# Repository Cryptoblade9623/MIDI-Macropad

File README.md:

# MIDI-Macropad
A MIDI macropad with 6 mechanical switches, per-key RGB, a rotary encoder and 7 capacitive touch keys. 
It is powered using a 2000mah battery and a TP4056 module. It is controlled by a Waveshare ESP32-S3-Zero. It can turn on and off using a rocker switch. 
This is a project for Half-Life at Hack club. This project's guide was made by [Kai Pereira](https://github.com/KaiPereira).
I have made my adjustments from the original project like adding more switches, more LEDs, making a themed case and making it battery powered. 
As I already have the keycaps and rocker switches and I will buy the lights and case myself, I will not include them in the Half-Life BOM, but they will be located in the readme for anyone who wants to make it from scratch. 
The files will include all 3D models used ( 3D printed parts and separate models online that i used for designing ), KiCad files and firmware. 
I tried to make as much as I could with the use of LLMs and I almost finished but I had to use AI to code the capacitive touch keys because I couldn't find documentation for that anywhere.
Everything but the capacitive touch keys section is code written/typed by hand.
The images below are screenshots of: what the project should look like after finished, PCB 3D models, offboard wired components, KiCad PCB and KiCad schematics in that order.

| Item                       | Qty | Supplier                   | Cost/item | Total Cost | link                                                                                                                                                                                                                                                                                                                                                                                                                                                                                                                                                                                                                                                                                                                                                                                                                                                                                                                                                                                                                 |
|----------------------------|-----|----------------------------|-----------|------------|----------------------------------------------------------------------------------------------------------------------------------------------------------------------------------------------------------------------------------------------------------------------------------------------------------------------------------------------------------------------------------------------------------------------------------------------------------------------------------------------------------------------------------------------------------------------------------------------------------------------------------------------------------------------------------------------------------------------------------------------------------------------------------------------------------------------------------------------------------------------------------------------------------------------------------------------------------------------------------------------------------------------|
| EC11 Rotary Encoder        | 1   | AliExpress                 | $2.04     | $2.04      | https://www.aliexpress.com/item/1005008973821901.html?spm=a2g0o.productlist.main.61.5bdd101emPDBlZ&algo_pvid=73940321-b95f-4575-a293-c059ac68aa32&algo_exp_id=73940321-b95f-4575-a293-c059ac68aa32-58&pdp_ext_f=%7B%22order%22%3A%2242%22%2C%22eval%22%3A%221%22%2C%22fromPage%22%3A%22search%22%7D&pdp_npi=6%40dis%21USD%212.04%212.03%21%21%2113.57%2113.50%21%4021038a9c17927755863875781e0e0a%2112000047424950599%21sea%21GB%210%21ABX%211%210%21n_tag%3A-29910%3Bd%3Ad6cd2d24%3Bm03_new_user%3A-29895%3BpisId%3A5000000218644952&curPageLogUid=blD9KSLR4E14&utparam-url=scene%3Asearch%7Cquery_from%3A%7Cx_object_id%3A1005008973821901%7C_p_origin_prod%3A                                                                                                                                                                                                                                                                                                                  |
| ESP32-S3-Zero              | 1   | AliExpress                 | $4.76     | $4.76      | https://www.aliexpress.com/item/1005007948911104.html?spm=a2g0o.productlist.main.29.238369f4yT16e8&algo_pvid=caeeea92-3d00-4a40-bc0e-dfc0eba1c6cb&algo_exp_id=caeeea92-3d00-4a40-bc0e-dfc0eba1c6cb-28&pdp_ext_f=%7B%22order%22%3A%221234%22%2C%22spu_best_type%22%3A%22price%22%2C%22eval%22%3A%221%22%2C%22fromPage%22%3A%22search%22%7D&pdp_npi=6%40dis%21USD%213.62%213.61%21%21%2124.06%2123.99%21%402103849717926670627467357e0dee%2112000051591697058%21sea%21GB%210%21ABX%211%210%21n_tag%3A-29910%3Bd%3Ad6cd2d24%3Bm03_new_user%3A-29895%3BpisId%3A5000000218644952&curPageLogUid=fZAsHxCwW0Vm&utparam-url=scene%3Asearch%7Cquery_from%3A%7Cx_object_id%3A1005007948911104%7C_p_origin_prod%3A                                                                                                                                                                                                                                                                                                               |
| OUTEMU Mechanical Switches | 1   | AliExpress                 | $3.48     | $3.48      | https://www.aliexpress.com/item/1005008210158349.html?spm=a2g0o.productlist.main.1.431a286fu5XIFE&algo_pvid=c54de943-8488-4a99-b3c9-1087a205fbdd&algo_exp_id=c54de943-8488-4a99-b3c9-1087a205fbdd-0&pdp_ext_f=%7B%22order%22%3A%22342%22%2C%22eval%22%3A%221%22%2C%22fromPage%22%3A%22search%22%7D&pdp_npi=6%40dis%21USD%213.48%211.35%21%21%213.48%211.35%21%402103828617924316227855893e10b3%2112000044245885241%21sea%21GB%210%21ABX%211%210%21n_tag%3A-29910%3Bd%3Ad6cd2d24%3Bm03_new_user%3A-29895%3BpisId%3A5000000218643717&curPageLogUid=KWfBJ2vS2QvT&utparam-url=scene%3Asearch%7Cquery_from%3A%7Cx_object_id%3A1005008210158349%7C_p_origin_prod%3A                                                                                                                                                                                                                                                                                                                                                        |
| PCB                        | 1   | JLCPCB                     | $9.10     | $9.10      | https://cart.jlcpcb.com/shopcart/cartEdit/?id=0b54ba9c2a9749e79611989d17219a13&type=1&changeType=1&achieveDate=72                                                                                                                                                                                                                                                                                                                                                                                                                                                                                                                                                                                                                                                                                                                                                                                                                                                                                                    |
| TP4056 Module              | 1   | AliExpress                 | $1.11     | $1.11      | https://www.aliexpress.com/item/1005012010859998.html?spm=a2g0o.detail.pcDetailTopMoreOtherSeller.7.8b4fs1gQs1gQMz&gps-id=pcDetailTopMoreOtherSeller&scm=1007.40050.354490.0&scm_id=1007.40050.354490.0&scm-url=1007.40050.354490.0&pvid=6702e870-a7da-431f-965d-711fee851179&_t=gps-id%3ApcDetailTopMoreOtherSeller%2Cscm-url%3A1007.40050.354490.0%2Cpvid%3A6702e870-a7da-431f-965d-711fee851179%2Ctpp_buckets%3A668%232846%238115%232000&pdp_ext_f=%7B%22order%22%3A%224080%22%2C%22eval%22%3A%221%22%2C%22orig_sl_item_id%22%3A%221005012010859998%22%2C%22orig_item_id%22%3A%221005012545578213%22%2C%22sceneId%22%3A%2230050%22%2C%22fromPage%22%3A%22recommend%22%7D&pdp_npi=6%40dis%21USD%212.23%211.11%21%21%2114.83%217.42%21%4021038db317926605102783847e0f16%2112000059351234419%21rec%21GB%21%21ABX%211%210%21n_tag%3A-29910%3Bd%3Ad6cd2d24%3Bm03_new_user%3A-29895&utparam-url=scene%3ApcDetailTopMoreOtherSeller%7Cquery_from%3A%7Cx_object_id%3A1005012010859998%7C_p_origin_prod%3A1005012545578213 |
| Battery                    | 1   | AliExpress                 | $5.99     | $5.99      | https://www.aliexpress.com/item/1005005614561610.html?spm=a2g0o.detail.pcDetailTopMoreOtherSeller.10.47f71UA91UA9tm&gps-id=pcDetailTopMoreOtherSeller&scm=1007.40050.354490.0&scm_id=1007.40050.354490.0&scm-url=1007.40050.354490.0&pvid=a5e69e93-03ff-41cb-8222-ed78d5e98786&_t=gps-id%3ApcDetailTopMoreOtherSeller%2Cscm-url%3A1007.40050.354490.0%2Cpvid%3Aa5e69e93-03ff-41cb-8222-ed78d5e98786%2Ctpp_buckets%3A668%232846%238111%231996&pdp_ext_f=%7B%22order%22%3A%22664%22%2C%22eval%22%3A%221%22%2C%22sceneId%22%3A%2230050%22%2C%22fromPage%22%3A%22recommend%22%7D&pdp_npi=6%40dis%21USD%215.99%211.35%21%21%215.99%211.35%21%40210381f017926611875426069e0e8c%2112000040028049695%21rec%21GB%21%21ABXZ%211%210%21n_tag%3A-29910%3Bd%3Ad6cd2d24%3Bm03_new_user%3A-29895%3BpisId%3A5000000218642852&utparam-url=scene%3ApcDetailTopMoreOtherSeller%7Cquery_from%3A%7Cx_object_id%3A1005005614561610%7C_p_origin_prod%3A                                                                                     |
| SK6812MINI-E RGB Lights    | 10  | Alibaba                    | $0.16     | $1.60      | https://www.alibaba.com/product-detail/Good-Quality-RGB-LED-SK6812MINI-E_1601785986306.html?spm=a2756.trade-carp.valid-supplier.2.21183192jbIMls                                                                                                                                                                                                                                                                                                                                                                                                                                                                                                                                                                                                                                                                                                                                                                                                                                                                     |
| 3D Printed Case            | 1   | Printer on Printing Legion | $2.67     | $2.67      | https://app.slack.com/client/E09V59WQY1E/C083P4FJM46                                                                                                                                                                                                                                                                                                                                                                                                                                                                                                                                                                                                                                                                                                                                                                                                                                                                                                                                                                 |
| Estimated total shipping   | 1   |                            |           | $6.06      |                                                                                                                                                                                                                                                                                                                                                                                                                                                                                                                                                                                                                                                                                                                                                                                                                                                                                                                                                                                                                      |
| Grand Total                |     |                            |           | $36.04     |                                                                                                                                                                                                                                                                                                                                                                                                                                                                                                                                                                                                                                                                                                                                                                                                                                                                                                                                                                                                                      |

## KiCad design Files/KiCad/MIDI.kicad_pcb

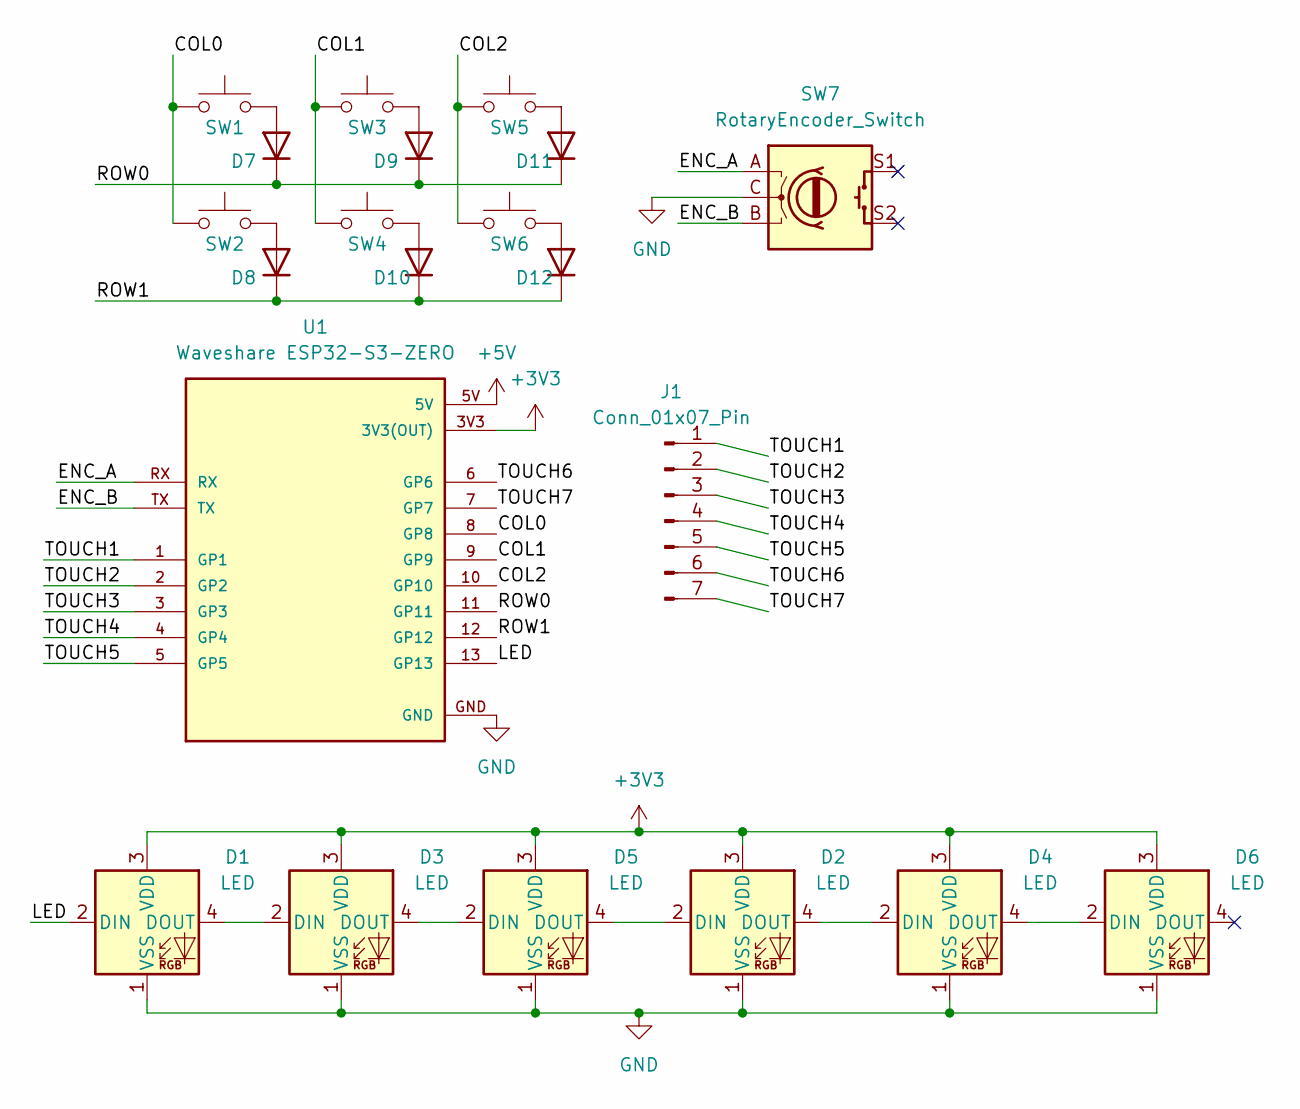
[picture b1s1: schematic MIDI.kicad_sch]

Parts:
D1, D2, D3, D4, D5, D6: LED; LED_MX_6028R
D7, D8, D9, D10, D11, D12: D; D_SOD-123
J1: Conn_01x07_Pin; Capacitive_PADS_7_25mm
SW1, SW2, SW3, SW4, SW5, SW6: SW_Push; SW_MX_HS_CPG151101S11_1u
SW7: RotaryEncoder_Switch; RotaryEncoder_Alps_EC11E-Switch_Vertical_H20mm
U1: Waveshare ESP32-S3-ZERO; Waveshare ESP32-S3-Zero; PARTREV NA

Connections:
+3V3: D1.3 (VDD), D2.3 (VDD), D3.3 (VDD), D4.3 (VDD), D5.3 (VDD), D6.3 (VDD), U1.3V3 (3V3(OUT))
+5V: U1.5V
/COL0: SW1.1, SW2.1, U1.8 (GP8)
/COL1: SW3.1, SW4.1, U1.9 (GP9)
/COL2: SW5.1, SW6.1, U1.10 (GP10)
/ENC_A: SW7.A, U1.RX
/ENC_B: SW7.B, U1.TX
/LED: D1.2 (DIN), U1.13 (GP13)
/ROW0: D7.1 (K), D9.1 (K), D11.1 (K), U1.11 (GP11)
/ROW1: D8.1 (K), D10.1 (K), D12.1 (K), U1.12 (GP12)
/TOUCH1: J1.1, U1.1 (GP1)
/TOUCH2: J1.2, U1.2 (GP2)
/TOUCH3: J1.3, U1.3 (GP3)
/TOUCH4: J1.4, U1.4 (GP4)
/TOUCH5: J1.5, U1.5 (GP5)
/TOUCH6: J1.6, U1.6 (GP6)
/TOUCH7: J1.7, U1.7 (GP7)
GND: D1.1 (VSS), D2.1 (VSS), D3.1 (VSS), D4.1 (VSS), D5.1 (VSS), D6.1 (VSS), SW7.C, U1.GND
unnamed: D1.4 (DOUT), D3.2 (DIN)
unnamed: D2.2 (DIN), D5.4 (DOUT)
unnamed: D2.4 (DOUT), D4.2 (DIN)
unnamed: D3.4 (DOUT), D5.2 (DIN)
unnamed: D4.4 (DOUT), D6.2 (DIN)
unnamed: D7.2 (A), SW1.2
unnamed: D8.2 (A), SW2.2
unnamed: D9.2 (A), SW3.2
unnamed: D10.2 (A), SW4.2
unnamed: D11.2 (A), SW5.2
unnamed: D12.2 (A), SW6.2

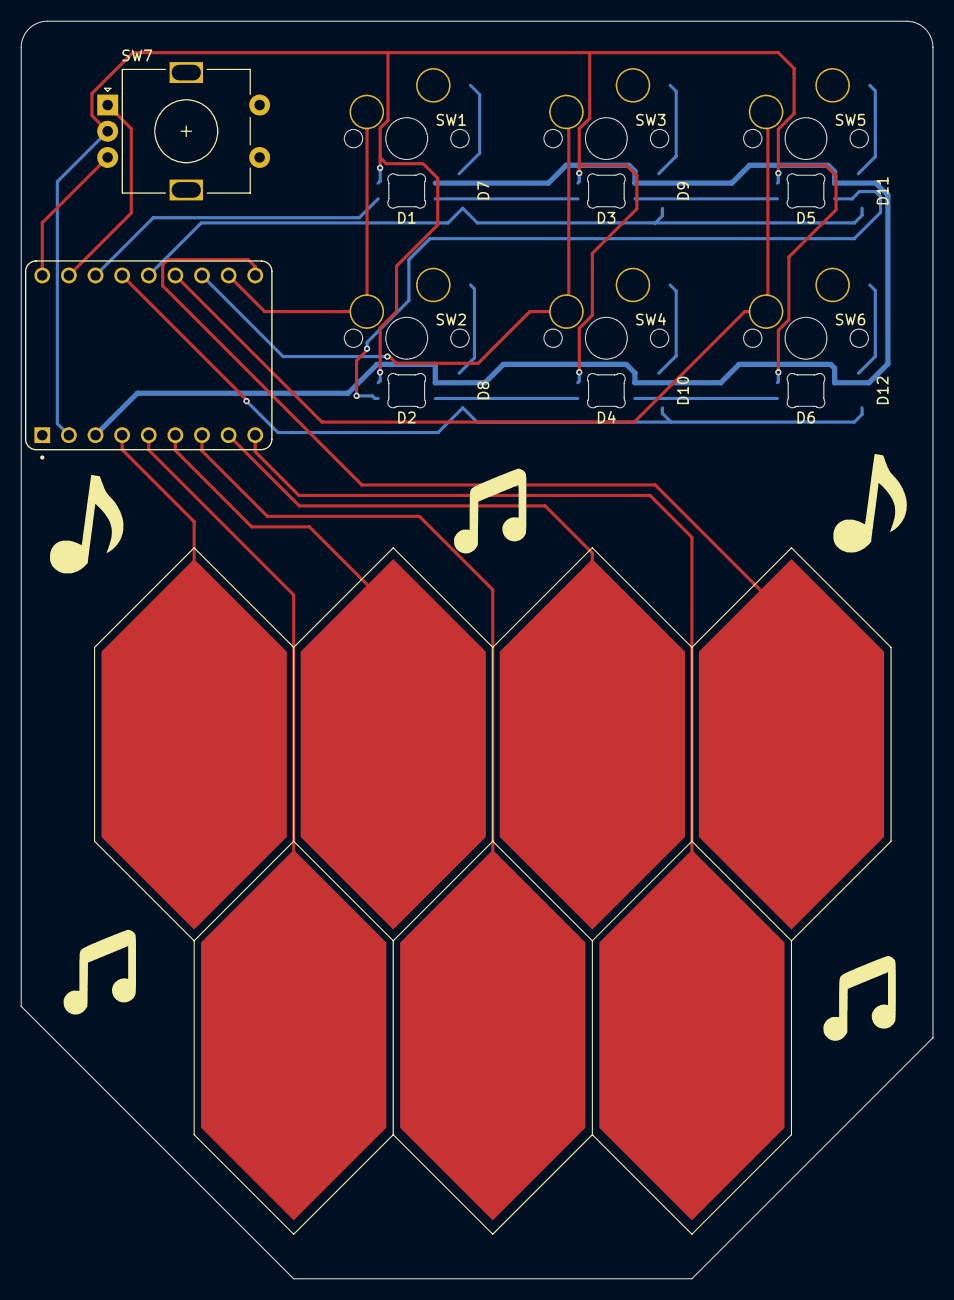
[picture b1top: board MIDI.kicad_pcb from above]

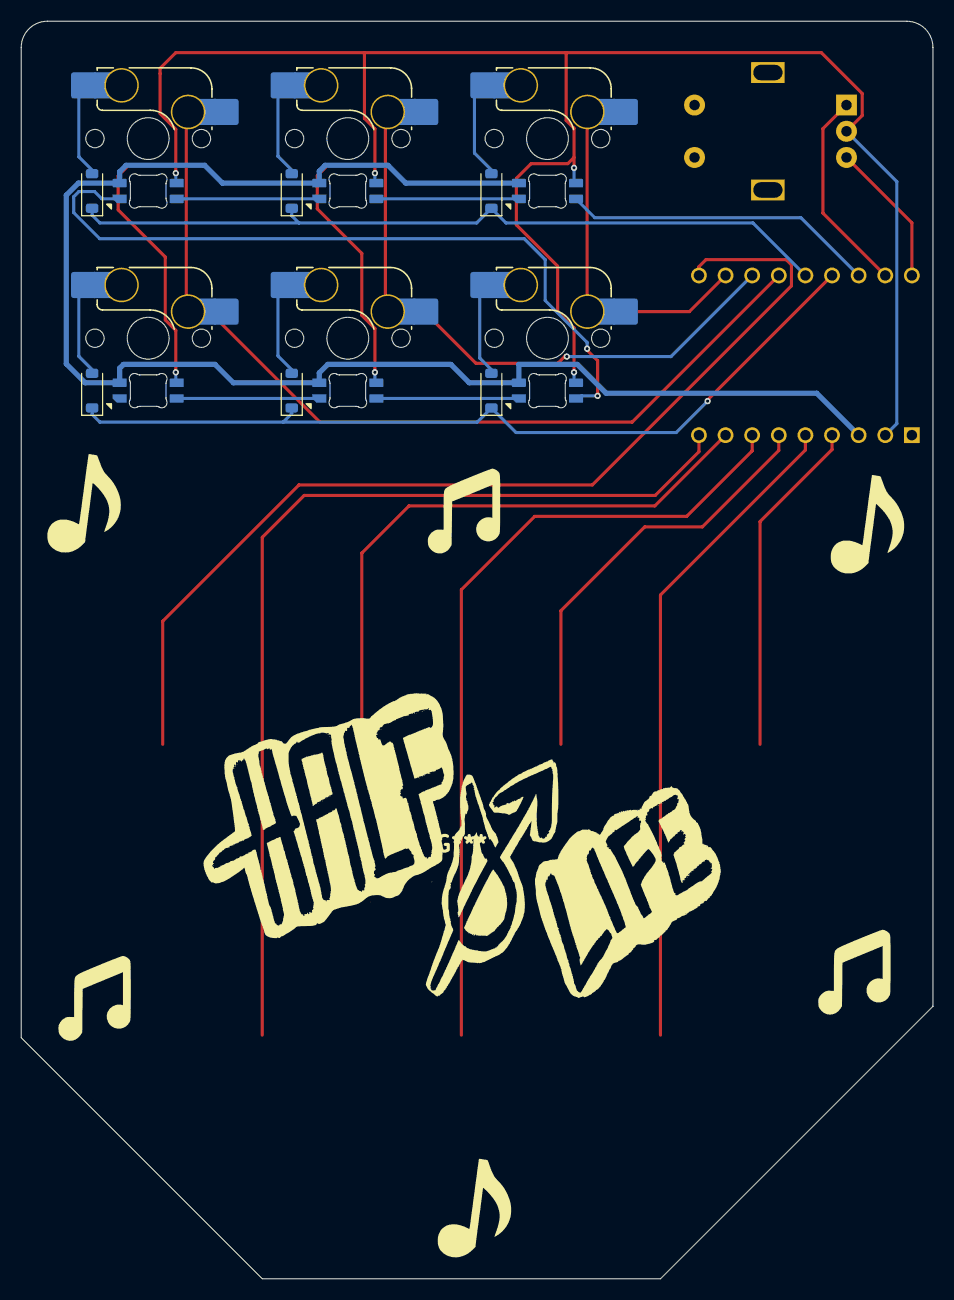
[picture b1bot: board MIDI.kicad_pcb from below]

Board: 2 copper layers, 87.0 x 120.0 mm, 21 parts (18 on the bottom side), 28 nets.

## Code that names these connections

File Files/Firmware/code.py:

print("Starting")

import board
import touchio

from kmk.kmk_keyboard import KMKKeyboard
from kmk.keys import KC
from kmk.scanners import DiodeOrientation
from kmk.modules.encoder import EncoderHandler
from kmk.extensions.rgb import RGB
from kmk.extensions.rgb import AnimationModes
from kmk.extensions.media_keys import MIDI
from kmk.extensions import Extension

keyboard = KMKKeyboard()

COL1 = board.IO8
COL2 = board.IO9
COL3 = board.IO10
ROW1 = board.IO11
ROW2 = board.IO12
ENC_A = board.RX
ENC_B = board.TX
LED = board.IO13

TOUCH_PINS = [
    board.IO1, 
    board.IO2, 
    board.IO3, 
    board.IO4, 
    board.IO5, 
    board.IO6, 
    board.IO7, 
]

TOUCH_NOTES = [60, 62, 64, 65, 67, 69, 71]

class CapacitiveTouchMidi(Extension):
    def __init__(self, pins, notes):
        self.touch_pads = [touchio.TouchIn(pin) for pin in pins]
        self.notes = notes
        self.pad_states = [False] * len(pins)

    def on_runtime_enable(self, sandbox):
        return

    def on_runtime_disable(self, sandbox):
        return

    def during_bootup(self, sandbox):
        return

    def before_matrix_scan(self, sandbox):
        for i, pad in enumerate(self.touch_pads):
            is_touched = pad.value
            if is_touched and not self.pad_states[i]:
                sandbox.extensions.MIDI.send_note_on(self.notes[i], 127)
                self.pad_states[i] = True
            elif not is_touched and self.pad_states[i]:
                sandbox.extensions.MIDI.send_note_off(self.notes[i], 0)
                self.pad_states[i] = False

    def after_matrix_scan(self, sandbox):
        return

    def before_hid_send(self, sandbox):
        return

    def after_hid_send(self, sandbox):
        return

touch_midi_ext = CapacitiveTouchMidi(TOUCH_PINS, TOUCH_NOTES)
keyboard.extensions.append(touch_midi_ext)

keyboard.col_pins = (COL1,COL2,COL3)
keyboard.row_pins = (ROW1,ROW2)
keyboard.diode_orientation = DiodeOrientation.COL2ROW

keyboard.keymaps = [
    [KC.ESC, KC.DELETE, KC.PSCREEN,
     KC.LEFT, KC.PAUSE, KC.RIGHT,
    ]
]

encoder_handler = EncoderHandler()
keyboard.modules.append(encoder_handler)
encoder_handler.pins = ((ENC_A, ENC_B, None, False),)
encoder_handler.map = (((KC.VOLD, KC.VOLU),),)

rgb_ext = RGB(
    pixel_pin = LED,
    num_pixels = 6,
    val_limit = 100,
    val_default = 75,
    animation_speed = 1,
    animation_mode = AnimationModes.KNIGHT,
    refresh_rate = 50,
)
keyboard.extensions.append(rgb_ext)

midi = MIDI()
keyboard.extensions.append(midi)

if __name__ == '__main__':
    keyboard.go()
